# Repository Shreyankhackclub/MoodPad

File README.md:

# MoodPad
A mood-aware macropad with GRIND and CHILL modes.
# MoodPad

A mood-aware macropad with GRIND and CHILL modes.

## Features

- Seeeduino XIAO microcontroller
- 0.91" OLED display
- Rotary encoder with push button
- 8-key matrix
- Custom PCB designed in KiCad
- Custom enclosure designed in Tinkercad
- Dual operating modes

## Modes

### ⚡ GRIND

- ChatGPT
- GitHub
- KiCad
- Notion
- Google Drive
- Google Docs
- Screenshot
- Focus Timer

### 🌙 CHILL

- Spotify
- YouTube
- Discord
- Netflix
- Play/Pause
- Next Track
- Previous Track
- Mute

## Hardware

- Seeeduino XIAO
- 0.91" I2C OLED
- Rotary Encoder
- 8 Mechanical Switches

## Project Files

- PCB files in `/PCB`
- Firmware in `/Firmware`
- Enclosure files in `/Case`
- Screenshots in `/Images`

## Development

MoodPad was designed using KiCad for electronics and Tinkercad for the enclosure. The project combines PCB design, firmware architecture, and product design into a compact desktop macropad.

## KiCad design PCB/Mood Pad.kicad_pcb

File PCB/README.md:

# PCB

KiCad schematic, PCB layout, and Gerber files.

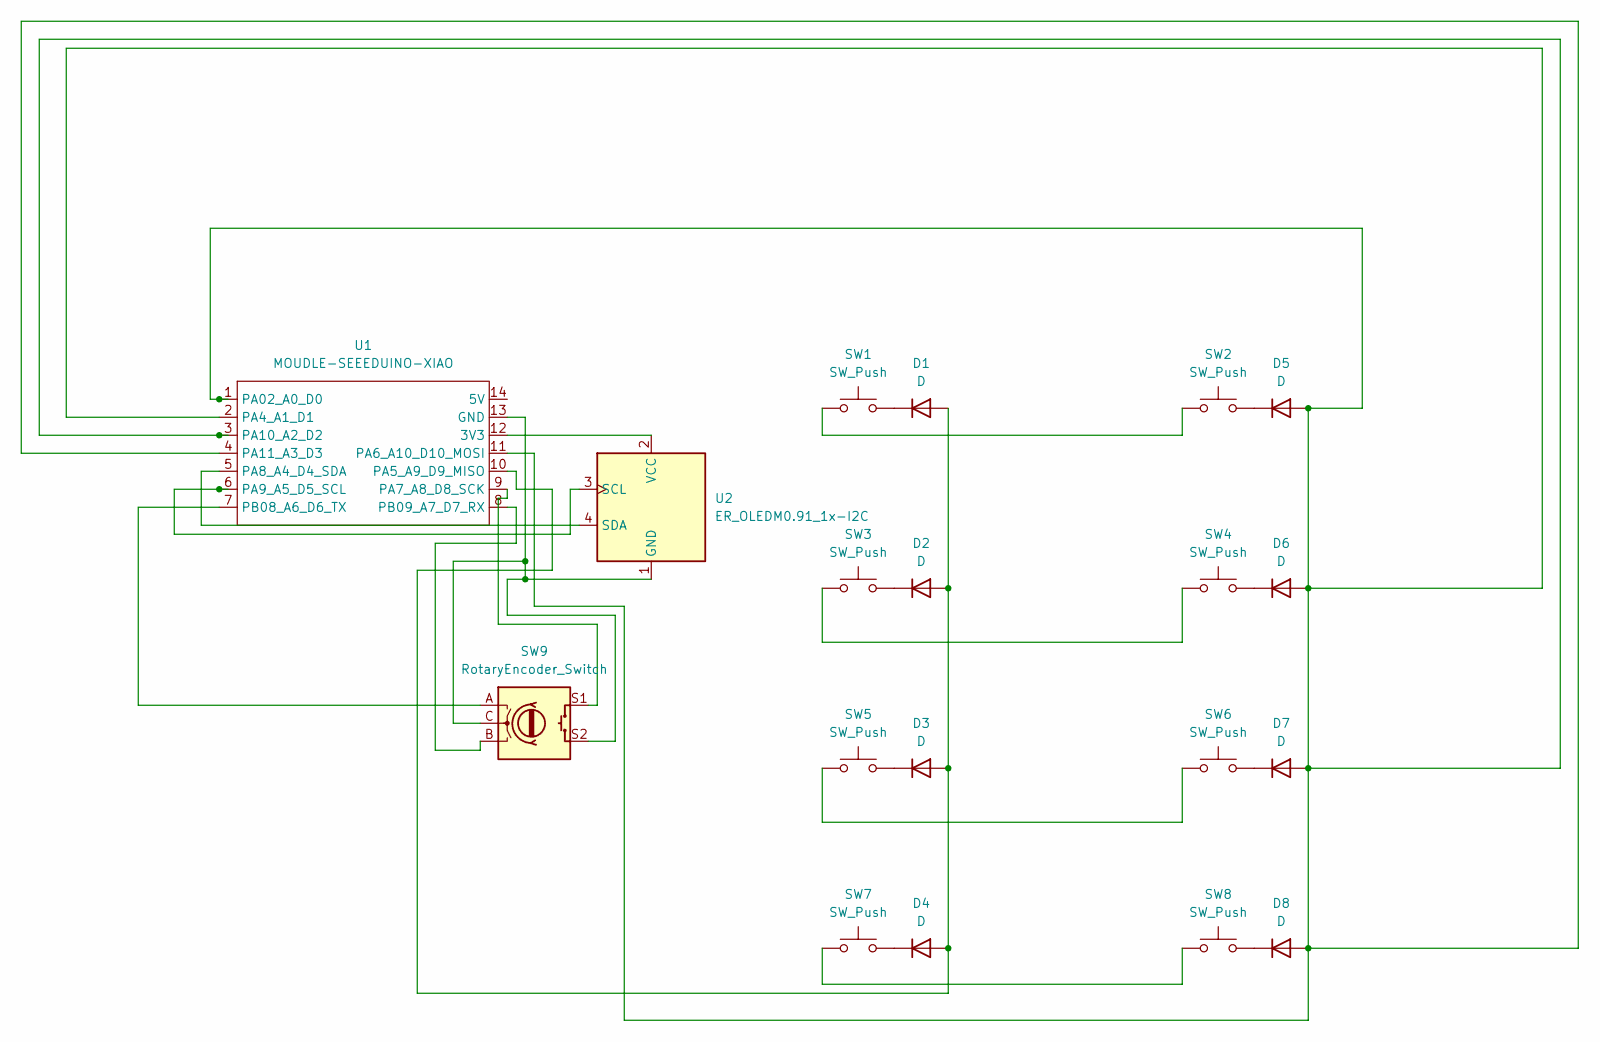
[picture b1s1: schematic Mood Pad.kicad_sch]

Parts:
D1, D2, D3, D4, D5, D6, D7, D8: D; D_DO-35_SOD27_P7.62mm_Horizontal
SW1, SW2, SW3, SW4, SW5, SW6, SW7, SW8: SW_Push; SW_Cherry_MX_1.00u_PCB
SW9: RotaryEncoder_Switch; RotaryEncoder_Alps_EC11E-Switch_Vertical_H20mm
U1: MOUDLE-SEEEDUINO-XIAO; XIAO-Generic-Hybrid-14P-2.54-21X17.8MM
U2: ER_OLEDM0.91_1x-I2C

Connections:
unnamed: D1.2 (A), D2.2 (A), D3.2 (A), D4.2 (A), U1.10 (PA5_A9_D9_MISO)
unnamed: D1.1 (K), SW1.2
unnamed: D2.1 (K), SW3.2
unnamed: D3.1 (K), SW5.2
unnamed: D4.1 (K), SW7.2
unnamed: D5.2 (A), D6.2 (A), D7.2 (A), D8.2 (A), U1.1 (PA02_A0_D0), U1.2 (PA4_A1_D1), U1.3 (PA10_A2_D2), U1.4 (PA11_A3_D3), U1.11 (PA6_A10_D10_MOSI)
unnamed: D5.1 (K), SW2.2
unnamed: D6.1 (K), SW4.2
unnamed: D7.1 (K), SW6.2
unnamed: D8.1 (K), SW8.2
unnamed: SW1.1, SW2.1
unnamed: SW3.1, SW4.1
unnamed: SW5.1, SW6.1
unnamed: SW7.1, SW8.1
unnamed: U1.12 (3V3), U2.2 (VCC)
unnamed: SW9.C, SW9.S2, U1.13 (GND), U2.1 (GND)
unnamed: SW9.S1, U1.9 (PA7_A8_D8_SCK)
unnamed: U1.5 (PA8_A4_D4_SDA), U2.4 (SDA)
unnamed: U1.6 (PA9_A5_D5_SCL), U2.3 (SCL)
unnamed: SW9.A, U1.7 (PB08_A6_D6_TX)
unnamed: SW9.B, U1.8 (PB09_A7_D7_RX)

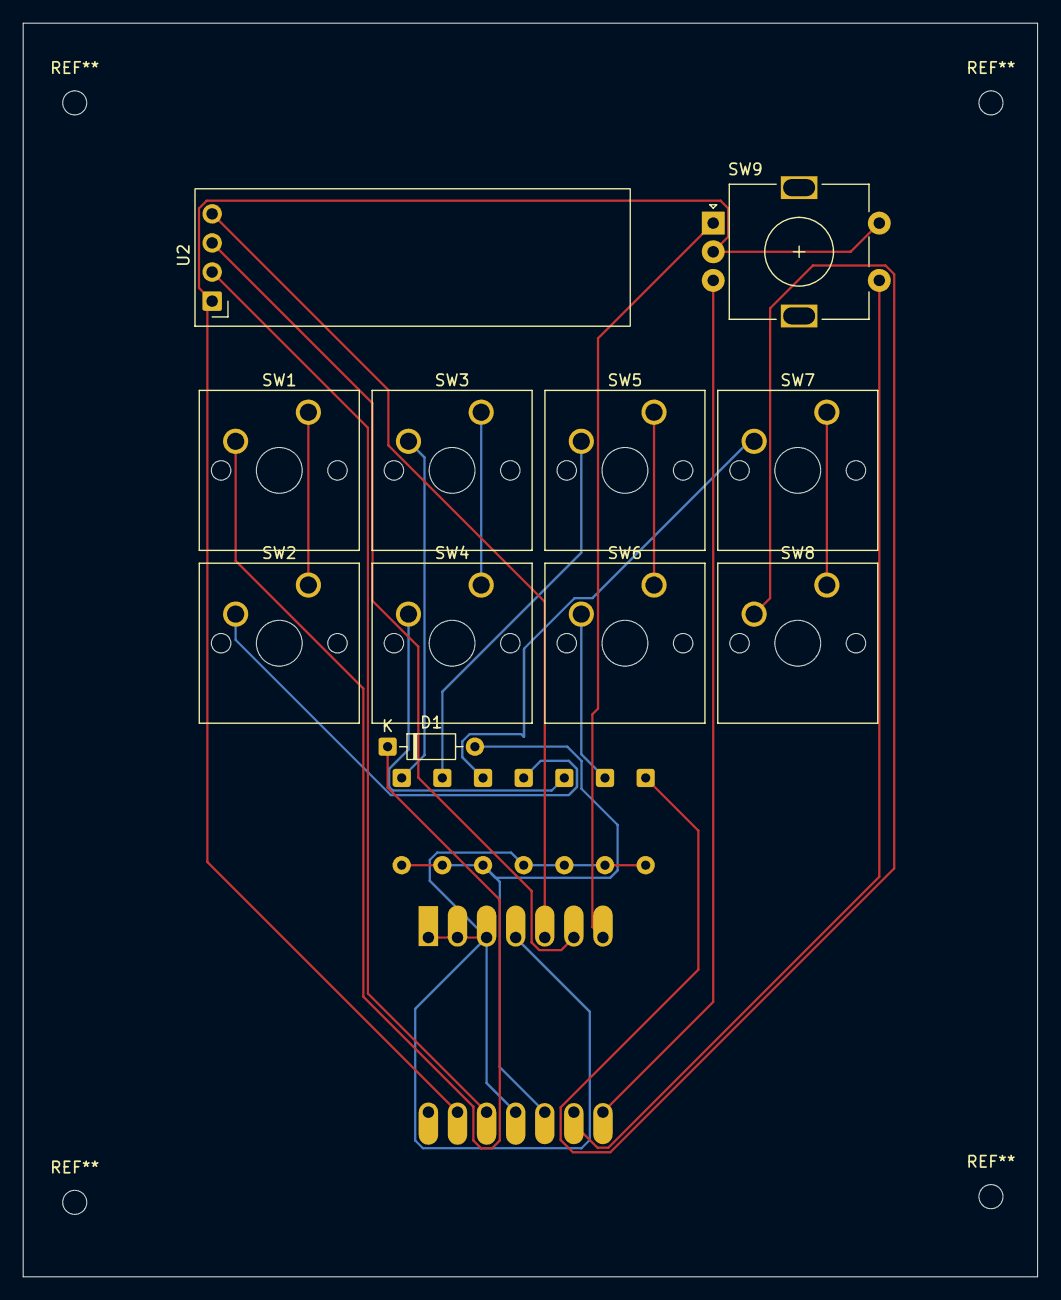
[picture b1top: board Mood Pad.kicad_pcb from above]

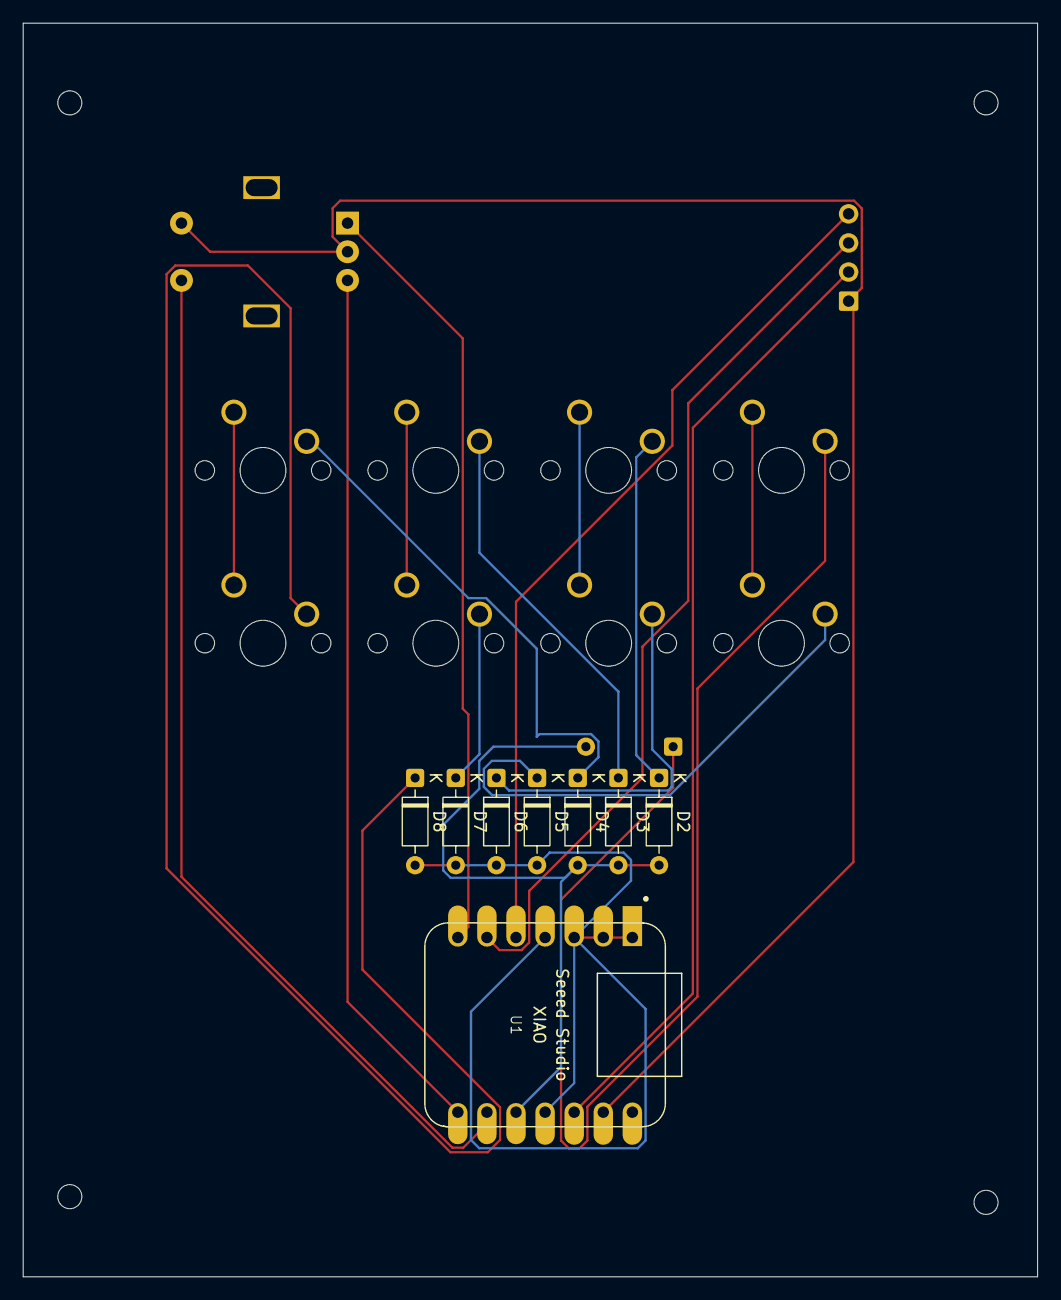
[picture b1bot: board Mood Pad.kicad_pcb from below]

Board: 2 copper layers, 88.6 x 109.5 mm, 19 parts (8 on the bottom side), 21 nets.
